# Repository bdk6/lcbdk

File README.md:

# lcbdk
L C meter based on Almost All Digital Electronics LC Meter written up in Nuts n Volts (Neil Hecht)

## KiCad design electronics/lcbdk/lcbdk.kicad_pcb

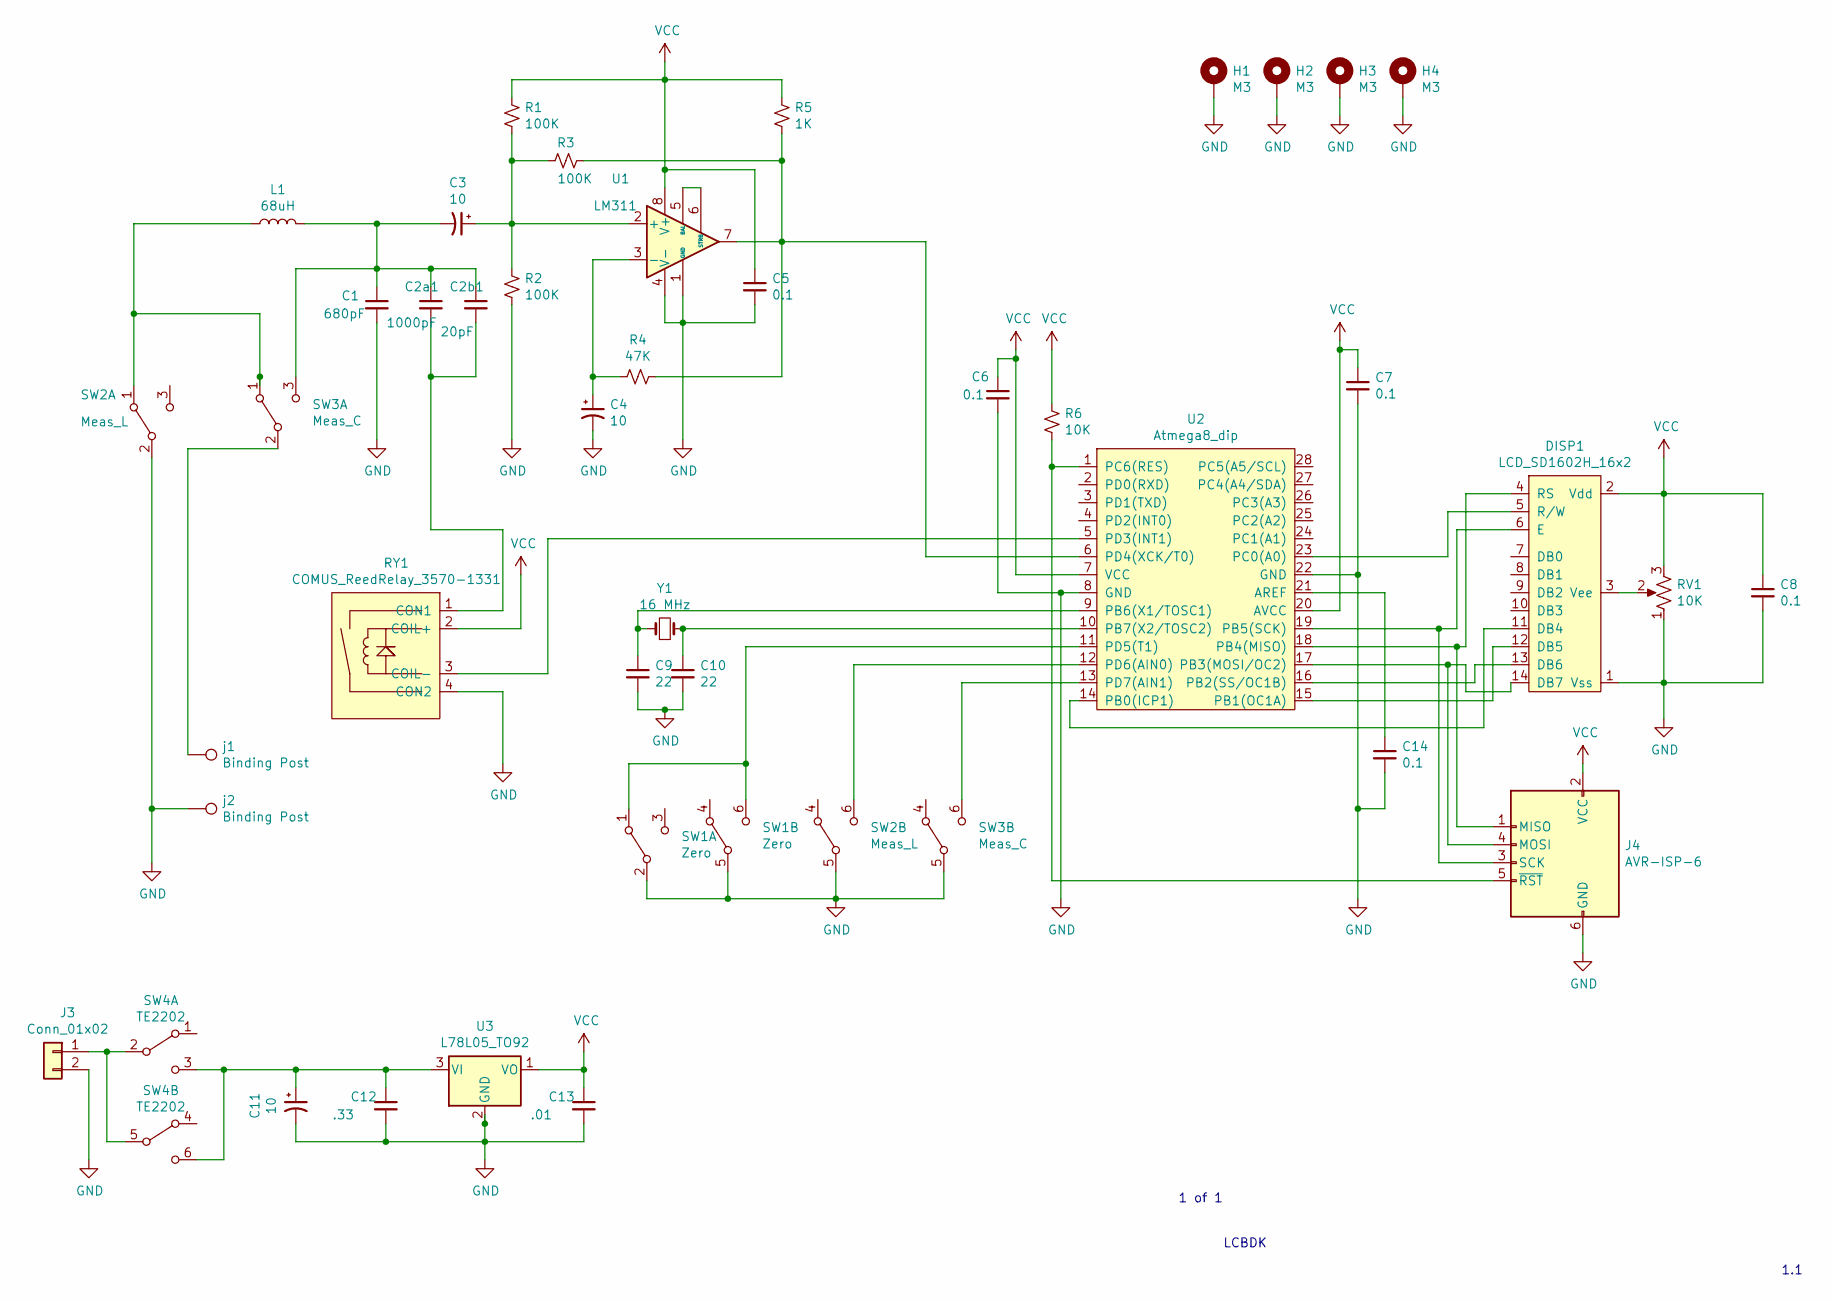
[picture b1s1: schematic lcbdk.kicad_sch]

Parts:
C1: 680pF; C_Disc_D4.7mm_W2.5mm_P5.00mm
C2a1: 1000pF; C_Disc_D4.7mm_W2.5mm_P5.00mm
C2b1: 20pF; C_Disc_D4.7mm_W2.5mm_P5.00mm
C3, C4, C11: 10; C_Disc_D4.7mm_W2.5mm_P5.00mm
C5, C6, C7, C8, C14: 0.1; C_Disc_D4.7mm_W2.5mm_P5.00mm
C9, C10: 22; C_Disc_D4.7mm_W2.5mm_P5.00mm
C12: .33; C_Disc_D4.7mm_W2.5mm_P5.00mm
C13: .01; C_Disc_D4.7mm_W2.5mm_P5.00mm
DISP1: LCD_SD1602H_16x2; LCD_SD1602H
H1, H2, H3, H4: M3; MountingHole_3.2mm_M3_DIN965_Pad
J3: Conn_01x02; PinHeader_1x02_P2.54mm_Vertical
J4: AVR-ISP-6; PinHeader_2x03_P2.54mm_Vertical
L1: 68uH; L_Axial_L7.0mm_D3.3mm_P10.16mm_Horizontal_Fastron_MICC
R1, R2, R3: 100K; R_Axial_DIN0207_L6.3mm_D2.5mm_P10.16mm_Horizontal
R4: 47K; R_Axial_DIN0207_L6.3mm_D2.5mm_P10.16mm_Horizontal
R5: 1K; R_Axial_DIN0207_L6.3mm_D2.5mm_P10.16mm_Horizontal
R6: 10K; R_Axial_DIN0207_L6.3mm_D2.5mm_P10.16mm_Horizontal
RV1: 10K; Tayda_Tokyo_Denshi_RM065_trimmer
RY1: COMUS_ReedRelay_3570-1331; COMUS_Relay_35701331
SW1: Zero; ESwitch_TL2202_DPDT
SW2: Meas_L; ESwitch_TL2202_DPDT
SW3: Meas_C; ESwitch_TL2202_DPDT
SW4: TE2202; ESwitch_TL2202_DPDT
U1: LM311; DIP-8_W7.62mm_LongPads
U2: Atmega8_dip; DIP-28_W7.62mm_Socket_LongPads
U3: L78L05_TO92; TO-92_Inline
Y1: 16 MHz; Crystal_HC49-U_Vertical
j1, j2: Binding Post; tayda_binding_post

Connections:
GND: C1.2, C4.2, C5.2, C6.2, C7.2, C8.2, C9.2, C10.2, C11.2, C12.2, C13.2, C14.2, DISP1.1 (Vss), H1.1, H2.1, H3.1, H4.1, J3.2, J4.6 (GND), R2.2, RV1.1, RY1.4 (CON2), SW1.2 (B), SW1.5 (B), SW2.2 (B), SW2.5 (B), SW3.5 (B), U1.1 (GND), U1.4 (V-), U2.8 (GND), U2.22 (GND), U3.2 (GND), j2.1
unnamed: C1.1, C2a1.1, C2b1.1, C3.2, L1.2, SW3.3 (C)
unnamed: C2a1.2, C2b1.2, RY1.1 (CON1)
unnamed: C3.1, R1.2, R2.1, R3.2, U1.2 (+)
unnamed: C4.1, R4.2, U1.3 (-)
unnamed: C9.1, U2.9 (PB6(X1/TOSC1)), Y1.1
unnamed: C10.1, U2.10 (PB7(X2/TOSC2)), Y1.2
unnamed: C11.1, C12.1, SW4.3 (C), SW4.6 (C), U3.3 (VI)
unnamed: C14.1, U2.21 (AREF)
unnamed: DISP1.3 (Vee), RV1.2
unnamed: DISP1.4 (RS), J4.1 (MISO), U2.18 (PB4(MISO))
unnamed: DISP1.5 (R/W), U2.23 (PC0(A0))
unnamed: DISP1.6 (E), J4.3 (SCK), U2.19 (PB5(SCK))
unnamed: DISP1.11 (DB4), U2.14 (PB0(ICP1))
unnamed: DISP1.12 (DB5), U2.15 (PB1(OC1A))
unnamed: DISP1.13 (DB6), U2.16 (PB2(SS/OC1B))
unnamed: DISP1.14 (DB7), J4.4 (MOSI), U2.17 (PB3(MOSI/OC2))
unnamed: J3.1, SW4.2 (B), SW4.5 (B)
unnamed: J4.5 (~RST), R6.2, U2.1 (PC6(RES))
unnamed: L1.1, SW2.1 (A), SW3.1 (A)
unnamed: R3.1, R4.1, R5.2, U1.7, U2.6 (PD4(XCK/T0))
unnamed: RY1.3 (COIL-), U2.5 (PD3(INT1))
unnamed: SW1.1 (A), SW1.6 (C), U2.11 (PD5(T1))
unnamed: SW2.6 (C), U2.12 (PD6(AIN0))
unnamed: SW3.2 (B), j1.1
unnamed: SW3.6 (C), U2.13 (PD7(AIN1))
unnamed: U1.5 (BAL), U1.6 (STRB)
VCC: C5.1, C6.1, C7.1, C8.1, C13.1, DISP1.2 (Vdd), J4.2 (VCC), R1.1, R5.1, R6.1, RV1.3, RY1.2 (COIL+), U1.8 (V+), U2.7 (VCC), U2.20 (AVCC), U3.1 (VO)

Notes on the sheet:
1.1
LCBDK
1 of 1

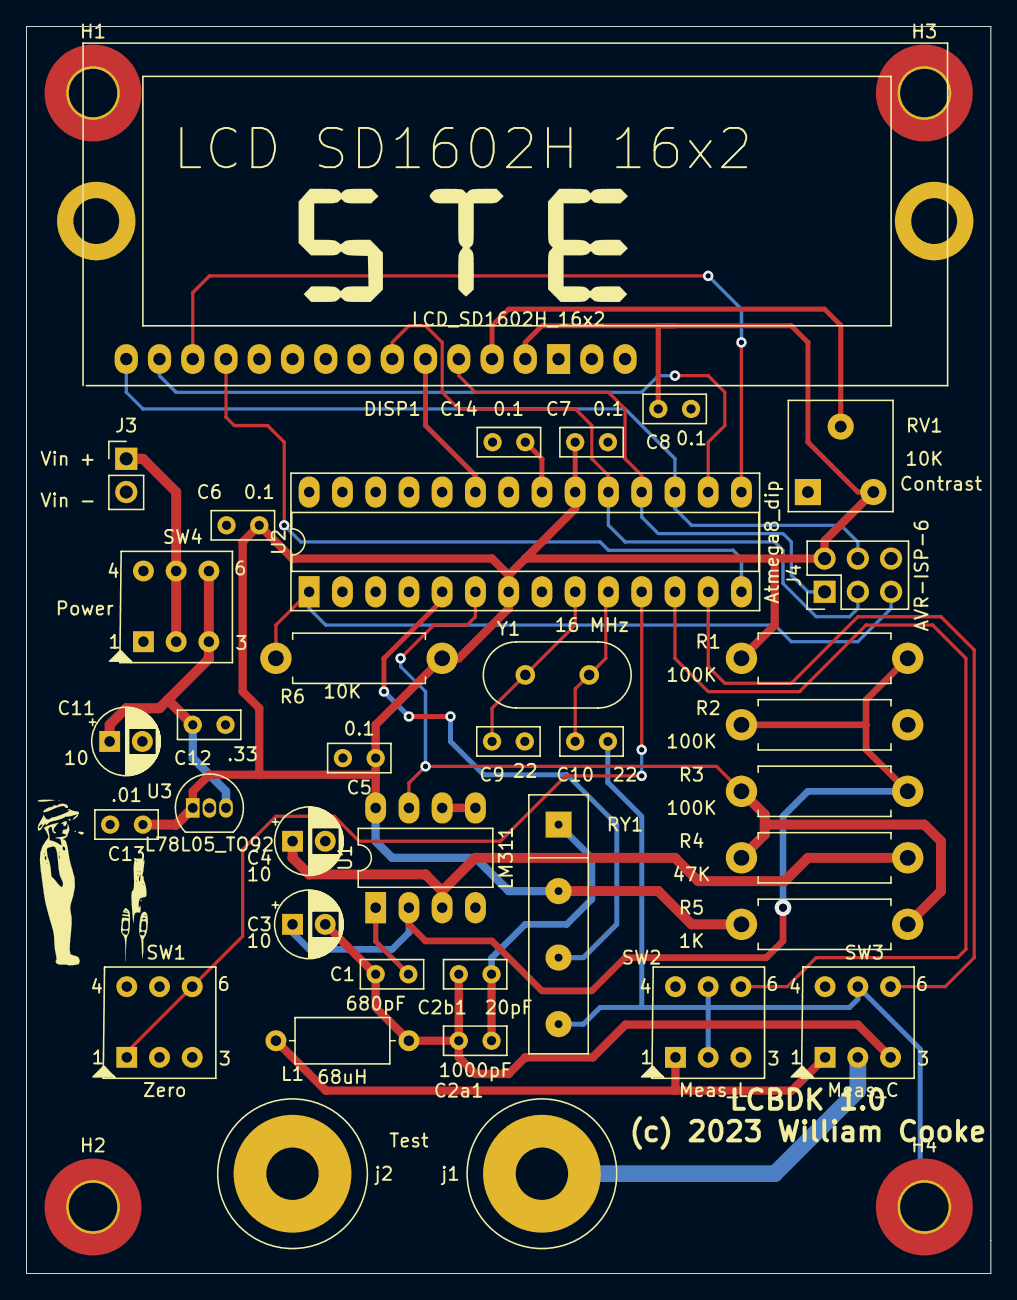
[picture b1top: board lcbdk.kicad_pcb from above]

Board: 2 copper layers, 73.7 x 95.2 mm, 41 parts (0 on the bottom side), 28 nets.

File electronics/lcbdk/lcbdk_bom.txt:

$Comp
F 0 "J3"  "Conn_01x02" 
$EndComp


$Comp
F 0 "SW4"  "TE2202" H 1650 7094 50  0000 C CNN
$EndComp


$Comp
F 0 "SW4" "TE2202" H 1650 6594 50  0000 C CNN
$EndComp


$Comp
F 0 "RV1"  "10K" H 9932 3895 50  0000 R CNN
$EndComp



$Comp
F 0 "C8" "0.1" H 10642 3805 50  0000 L CNN
$EndComp



$Comp
F 0 "C6" "0.1" H 6100 2750 50  0000 L CNN
$EndComp


$Comp
F 0 "C7"  "0.1" H 8392 2655 50  0000 L CNN
$EndComp


$Comp
F 0 "#PWR0101"  "VCC" H 4015 6573 50  0000 C CNN
$EndComp


$Comp
F 0 "C11"  V 2263 6700 50  0000 C CNN
$EndComp



$Comp
F 0 "C13"  ".01" H 3700 6650 50  0000 L CNN
$EndComp


$Comp
F 0 "C12"  ".33" H 2600 6650 50  0000 L CNN
$EndComp


$Comp
F 0 "#PWR0102"  "GND" H 3455 6827 50  0000 C CNN
$EndComp


$Comp
F 0 "U3"  "L78L05_TO92" H 3450 6651 50  0000 C CNN
$EndComp


$Comp
F 0 "#PWR0103" "GND" H 10005 4377 50  0000 C CNN
$EndComp


$Comp
F 0 "#PWR0104"  "VCC" H 10015 3273 50  0000 C CNN
$EndComp




$Comp
F 0 "DISP1"  "LCD_SD1602H_16x2" H 9450 3274 50  0000 C CNN
$EndComp



$Comp
F 0 "#PWR0105"  "VCC" H 8215 2623 50  0000 C CNN
$EndComp




$Comp
F 0 "C2b1"  "20pF" H 3200 2100 50  0000 L CNN
$EndComp


$Comp
F 0 "#PWR0106"  "VCC" H 6415 2673 50  0000 C CNN
$EndComp

$Comp
F 0 "#PWR0107"  "VCC" H 3665 3923 50  0000 C CNN
$EndComp

$Comp
F 0 "#PWR0108"  "VCC" H 6615 2673 50  0000 C CNN
$EndComp



$Comp
F 0 "#PWR0109"  "GND" H 3555 4627 50  0000 C CNN
$EndComp




$Comp
F 0 "RY1"  "COMUS_ReedRelay_3570-1331" H 3042 3824 50  0000 C CNN
$EndComp


$Comp
F 0 "j2"  "Binding Post" V 1845 5238 50  0000 L CNN
$EndComp


$Comp
F 0 "j1"  "Binding Post" V 1845 4938 50  0000 L CNN
$EndComp




$Comp
F 0 "#PWR0110"  "GND" H 1605 5177 50  0000 C CNN
$EndComp


$Comp
F 0 "SW1"  "Zero" V 4305 5062 50  0000 R CNN
$EndComp




$Comp
F 0 "#PWR0111"  "GND" H 8305 5377 50  0000 C CNN
$EndComp




$Comp
F 0 "#PWR0112"  "GND" H 6655 5377 50  0000 C CNN
$EndComp


$Comp
F 0 "#PWR0113"  "GND" H 4455 4327 50  0000 C CNN
$EndComp




$Comp
F 0 "SW1"  "Zero" V 4755 5012 50  0000 R CNN
$EndComp




$Comp
F 0 "SW3"  "Meas_C" V 5955 5012 50  0000 R CNN
$EndComp


$Comp
F 0 "SW3"  "Meas_C" V 2255 2662 50  0000 R CNN
$EndComp


$Comp
F 0 "SW2"  "Meas_L" V 5355 5012 50  0000 R CNN
$EndComp


$Comp
F 0 "SW2"  "Meas_L" V 1600 3300 50  0000 R CNN
$EndComp


$Comp
F 0 "Y1"  "16 MHz" H 4450 4184 50  0000 C CNN
$EndComp




$Comp
F 0 "U2"  "Atmega8_dip" H 7400 3124 50  0000 C CNN
$EndComp




$Comp
F 0 "#PWR0114"  "GND" H 4555 2827 50  0000 C CNN
$EndComp


$Comp
F 0 "#PWR0115"  "GND" H 3605 2827 50  0000 C CNN
$EndComp


$Comp
F 0 "#PWR0116"  "GND" H 4055 2827 50  0000 C CNN
$EndComp


$Comp
F 0 "#PWR0117"  "GND" H 5405 5377 50  0000 C CNN
$EndComp


$Comp
F 0 "#PWR0118"  "GND" H 1255 6827 50  0000 C CNN
$EndComp




$Comp
F 0 "R4"  "47K" V 4186 2650 50  0000 C CNN
$EndComp


$Comp
F 0 "R3"  "100K" V 4000 1500 50  0000 C CNN
$EndComp


$Comp
F 0 "R2"  "100K" H 3668 2105 50  0000 L CNN
$EndComp


$Comp
F 0 "L1"  "68uH" V 2399 1800 50  0000 C CNN
$EndComp


$Comp
F 0 "C3"  "10" V 3163 1800 50  0000 C CNN
$EndComp


$Comp
F 0 "C4"  "10" H 4141 2805 50  0000 L CNN
$EndComp


$Comp
F 0 "C5"  "0.1" H 5042 2105 50  0000 L CNN
$EndComp


$Comp
F 0 "C1"  "680pF" H 2550 2200 50  0000 L CNN
$EndComp


$Comp
F 0 "C2a1"  "1000pF" H 2900 2150 50  0000 L CNN
$EndComp


$Comp
F 0 "C10"  "22" H 4642 4255 50  0000 L CNN
$EndComp


$Comp
F 0 "C9"  "22" H 4392 4255 50  0000 L CNN
$EndComp


$Comp
F 0 "R1"  "100K" H 3668 1155 50  0000 L CNN
$EndComp


$Comp
F 0 "R5"  "1K" H 5168 1155 50  0000 L CNN
$EndComp


$Comp
F 0 "R6"  "10K" H 6668 2855 50  0000 L CNN
$EndComp
$Comp
F 0 "U1"  "LM311" H 4050 2100 50  0000 L CNN
$EndComp





$Comp
F 0 "#PWR0119"  "GND" H 2855 2827 50  0000 C CNN
$EndComp





$Comp
F 0 "C14" "0.1" 
$EndComp





$Comp
F 0 "J4"  "AVR-ISP-6" 
$EndComp

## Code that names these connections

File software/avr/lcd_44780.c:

//////////////////////////////////////////////////////////////////////////////
///  @file lcd_44780.c
///  copyright(c) 2023,2014 William R Cooke
///  @brief Interfaces AVR to character LCDs using HD44780 or compatible
//////////////////////////////////////////////////////////////////////////////

#define F_CPU 16000000
#include <avr/io.h>
#include <util/delay.h>
#include <stdint.h>

#include "lcd_44780.h"


#define CMD 0   // Select CMD reg
#define DAT 1   // Select DATA reg
#define RD  1   // Select READ mode
#define WR  0   // Select WRITE mode

static uint8_t columns = 8;
static uint8_t rows = 1;


// RS -> PB4
// RW -> PC0
// E  -> PB5
// D4 -> PB0
// D5 -> PB1
// D6 -> PB2
// D7 -> PB3




static void RS_set(int rs)
{
  if(rs)
    {
      PORTB |= (1 << 4);
    }
  else
    {
      PORTB &= ~(1 << 4);
    }

}

static void RW_set(int rw)
{
  if(rw)
    {
      PORTC |= (1 << 0);
    }
  else
    {
      PORTC &= ~(1<<0);
    }

}

static void E_set(int e) // pb5
{
  if(e)
    {
      PORTB |= (1<<5);
    }
  else
    {
      PORTB &= ~(1 << 5);
    }
}


static void wait(void)
{
}

static void write_nibble(uint8_t nib)
{
  nib &= 0x0f;  // Use only low four bits
  uint8_t tmp = PORTB;
  tmp &= 0xf0;  // Keep port's high bits as-is
  tmp |= nib;   // Merge the nibble bits
  PORTB = tmp;
  _delay_us(5);//5);
  E_set(1);
  _delay_us(5); //5);
  E_set(0);
  _delay_us(5); //5);
  
}


//////////////////////////////////////////////////////////////////////////////
///  \b LCD_44780_init
///  \brief Initializes LCD display
///  \param[in] num_cols Number of columns on display
///  \param[in] num_rows Number of rows on display
//////////////////////////////////////////////////////////////////////////////
void LCD_44780_init(uint8_t num_cols, uint8_t num_rows)
{
   columns = num_cols;
   rows = num_rows;

   DDRB |= (1 << 4);  // RS as output
   DDRC |= (1 << 0);  // RW as output
   DDRB |= (1 << 5);  // E as output
   DDRB |= 0x0f;      // D4 to D7 as output

   RS_set(0);  // Command mode
   RW_set(0);  // Write mode
   E_set(0);
   _delay_ms(15);  // wait for it to finish initialization
   // Set 4 bit mode
   write_nibble(3);
   _delay_us(20); //50);
   write_nibble(3);
   _delay_us(20); //50);
   write_nibble(2);
   _delay_us(20); //50);
   // Now set it how we want it
   LCD_44780_function_set(LCD_44780_TWO_LINES);
   LCD_44780_entry_mode(LCD_44780_INCREMENT);
   LCD_44780_display_enable(LCD_44780_ON); // turn on the display
   LCD_44780_clear();
   LCD_44780_home();
}

//////////////////////////////////////////////////////////////////////////////
///  \b LCD_44780_write_command
///  \brief Send a command to lcd
///  \param[in]  cmd  The command byte to send
//////////////////////////////////////////////////////////////////////////////
void LCD_44780_write_command( uint8_t cmd)
{
  RS_set(CMD);
  write_nibble( (cmd >> 4) & 0x0f );
  write_nibble( cmd & 0x0f );
  _delay_us(20); //50);
}

//////////////////////////////////////////////////////////////////////////////
///  \b LCD_44780_write_data
///  \param[in] data The data byte to write to LCD
/////////////////////////////////////////////////////////////////////////////
void LCD_44780_write_data(uint8_t data)
{
  RS_set(DAT);
  write_nibble( (data >> 4) & 0x0f );
  write_nibble( data & 0x0f );
  _delay_us(20); //50);
}

//////////////////////////////////////////////////////////////////////////////
/// \b LCD_44780_clear
/// \brief Clears display and sets address to 0
//////////////////////////////////////////////////////////////////////////////
void LCD_44780_clear(void)
{
  LCD_44780_write_command(0x01);
  _delay_ms(2);
}

//////////////////////////////////////////////////////////////////////////////
/// \b LCD_44780_home
/// \brief Homes cursor
//////////////////////////////////////////////////////////////////////////////
void LCD_44780_home(void)
{
  LCD_44780_write_command(0x02);
  _delay_ms(2);
}

//////////////////////////////////////////////////////////////////////////////
/// \b LCD_44780_entry_mode
/// \brief Sets cursor move directon and display shift on entry
/// @param[in] p Entry Mode enums or'ed together.
/// @param
//////////////////////////////////////////////////////////////////////////////
void LCD_44780_entry_mode(LCD_44780_param_t p)
{
  uint8_t cmd = 0x04;
  cmd |= p;
  LCD_44780_write_command(cmd);
  _delay_us(40);
}

//////////////////////////////////////////////////////////////////////////////
/// @fn LCD_44780_display_enable
/// @brief Enables or disables display, cursor, and blink
/// @param[in] p Display Enable enums or'ed together
//////////////////////////////////////////////////////////////////////////////
void LCD_44780_display_enable(int p)
{
  uint8_t cmd = 0x08;
  cmd |= p;
  LCD_44780_write_command(cmd);
  _delay_us(40);
}

//////////////////////////////////////////////////////////////////////////////
/// @fn LCD_44780_cursor_display_shift
/// @brief Sets cursor or display shift mode
/// @param[in] p Cursor Display Shift enums or'ed together.
//////////////////////////////////////////////////////////////////////////////
void LCD_44780_cursor_display_shift(int p)
{
  uint8_t cmd = 0x10;
  cmd |= p;
  LCD_44780_write_command(cmd);
  _delay_us(40);
}

//////////////////////////////////////////////////////////////////////////////
/// @fn LCD_44780_function_set
/// @brief SEts display length, lines, and font
/// @param[in] p Function Set enums or'ed together.
//////////////////////////////////////////////////////////////////////////////
void LCD_44780_function_set(int p)
{
  uint8_t cmd = 0x20;
  cmd |= p;
  LCD_44780_write_command(cmd);
  _delay_us(40);
}

//////////////////////////////////////////////////////////////////////////////
/// @fn LCD_44780_set_CGRAM_address
/// @brief Sets CGRAM address pointer.
/// @param[in] adr  Address to set.
//////////////////////////////////////////////////////////////////////////////
void LCD_44780_set_CGRAM_address(int adr)
{
  uint8_t cmd = 0x40 + (uint8_t)(adr & 0x3f);
  LCD_44780_write_command(cmd);
  _delay_us(40);
}

//////////////////////////////////////////////////////////////////////////////
/// @fn LCD_44780_set_DDRAM_address
/// @brief Sets DDRAM address pointer.
/// @param[in] adr Address to set.
//////////////////////////////////////////////////////////////////////////////
void LCD_44780_set_DDRAM_address(int adr)
{
  uint8_t cmd = 0x80 + (uint8_t)(adr & 0x7f);
  LCD_44780_write_command(cmd);
  _delay_us(40);
}

//////////////////////////////////////////////////////////////////////////////
/// @fn LCD_44780_goto
/// @brief Move cursor to column and row given
/// @param[in] col  Column to go to, 0 to 39
/// @param[in] row  Row to go to , 0 to 4.
/// @return Returns 1 if succesful, 0 if not
//////////////////////////////////////////////////////////////////////////////
uint8_t LCD_44780_goto(int col, int row)
{
  uint8_t rtn = 0;
  if(col < columns && row < rows)
    {
      rtn = 1;
      LCD_44780_set_DDRAM_address(row * 40 + col);
    }
  
  return rtn;
}

//////////////////////////////////////////////////////////////////////////////
/// @fn LCD_44780_read_status
/// @brief Reads busy flag and address.
/// @return Returns byte with busy flag and address.
//////////////////////////////////////////////////////////////////////////////
uint8_t LCD_44780_read_status(void)
{
  uint8_t rtn = 0;
  // TODO read byte here
  return rtn;
}

//////////////////////////////////////////////////////////////////////////////
/// @fn LCD_44780_read_data
/// @brief Reads data from display.
/// @return The data.
//////////////////////////////////////////////////////////////////////////////
uint8_t LCD_44780_read_data(void)
{
  uint8_t rtn = 0;
  // TODO add stuff here
  return rtn;
}


/////////////////////////////////////////////////////////////////////////////
///  \b LCD_44780_write_string
///  \param[in] str String to write, null terminated
/// @return Number of characters written.
//////////////////////////////////////////////////////////////////////////////
int LCD_44780_write_string(char* str)
{
  int cnt = 0;
  char ch;
  while( ch = *str )
    {
      cnt++;
      LCD_44780_write_data(ch);
      str++;
    }
  return cnt;
}

  

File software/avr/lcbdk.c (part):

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

// ///////////////////////////////////////////////////////////////////////////
// L measure button on PD7
// C measure button on PD6
// Zero button on PD5
// ///////////////////////////////////////////////////////////////////////////
typedef enum ButtonPress
{
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  //DDRD |= 0x01;  // D0 has LED
  //PORTD |= 0x01; // turn it on

  // set up for calibrate relay PD3
  PORTD |= (1<<3);  // turn it off 1=off, 0=on
  DDRD  |= (1<<3);  // make it an output
 
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
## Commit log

2021-07-13 Copied original Arduino code into repo.
2021-07-13 (re)created initial schematic
2022-09-20 Added docs
2023-03-07 Modified schematic and added basic working code.
2023-03-10 Enhanced code, added more to schematic.
2023-03-20 Updated schematic. More code. Added docs.
2023-04-02 Finished first iteration PCB.
2023-04-04 Final PCB design.
2023-05-17 Updated schematic, code, and Makefile
2023-05-25 Began match code.
2026-06-12 Added lots of files.

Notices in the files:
electronics/lcbdk/lcbdk.kicad_pcb:
(c) 2023 William R Cooke / Small Time Electronics
(c) 2023 William Cooke
